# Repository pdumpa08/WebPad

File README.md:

# WebPad

WebPad is a macropad made for web developers everywhere. It uses a system of 5 custom-mapped keys to offer developers the increased efficiency you need when on a tight deadline. It also includes two RGB LEDs (for that extra coolness factor) and uses KMK firmware to control everything.

## Features:
- 3D printed case
- 2RGB SK6812MINI LEDs for underglow (open to customization)
- 5 custom-mapped keys (Cherry MX keys)
- All code using kmk firmware (easy to modfiy if you know Python)

## CAD Model:
Everything fits together using 4 M3 screws and heatset inserts, used on the case

It has 2 separate printed pieces: the top section and the bottom section. These sections fit together using the screws mentioned above. These designs were created on Fusion 360, with fit tests done for each of the parts (including with the PCB).

## PCB:
Below are my PCB design and schematic. I designed the schematic/PCB to match the needs of web developers, with 5 switches offering access to essential functions (described in the firmware section). Basic connection techniques like using both layers for traces were required and implemented. After a little research, I found that using a ground plane will likely improve functionality in this product.

## Firmware:
This hackpad uses KMK firmware for everything, from mapping the switches to controlling the LEDs. Specifically, the firmware currently offers this functionality:

- RGB LED backlighting
- refresh web page
- clear cache in a browser
- open elements in browser developer tools
- open responsive design mode
- start VSCode Live Server
- open console in developer tools

## BOM:

Here is everything you need to make this hackpad (All parts part of the approved kit)

- 5x Cherry MX Switches
- 5x DSA Keycaps
- 4x M3x5x4 Heatset inserts
- 4x M3x16mm screws
- 2x SK6812 MINI-E LEDs
- 1x XIAO RP2040
- 1x Case (2 printed parts)

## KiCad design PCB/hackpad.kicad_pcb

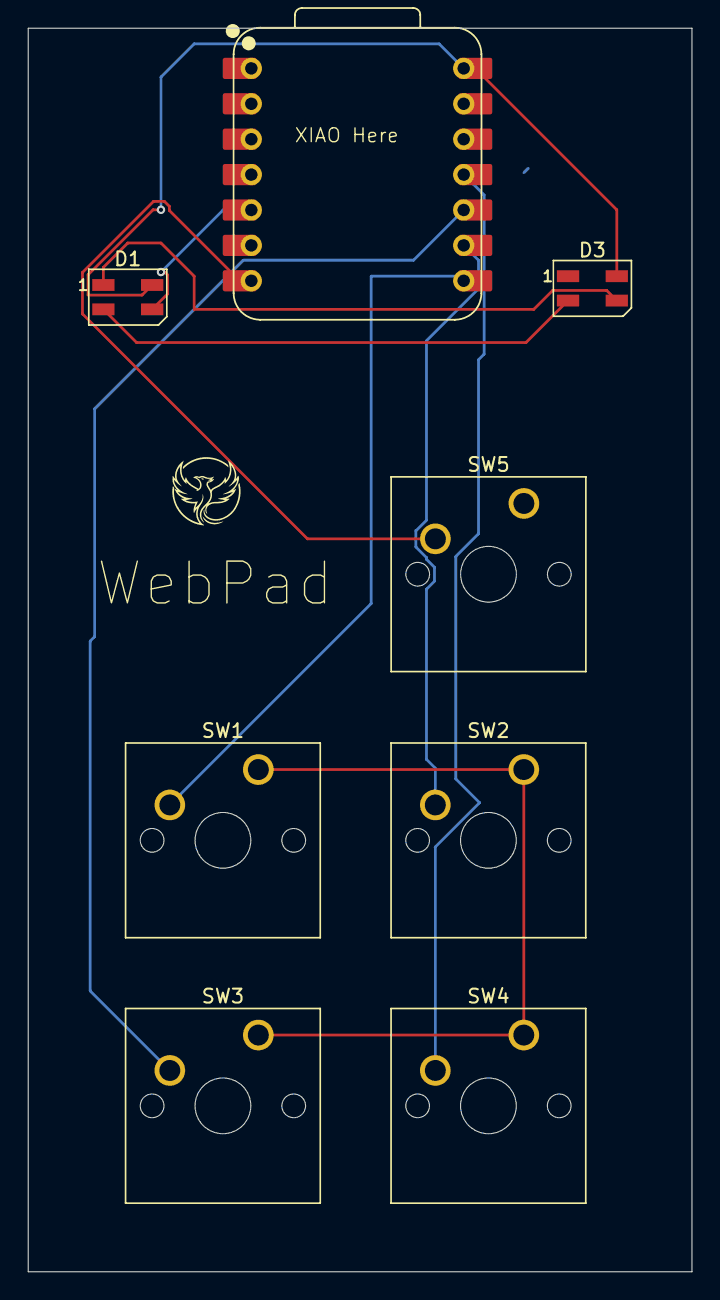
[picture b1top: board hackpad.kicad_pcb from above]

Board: 2 copper layers, 47.6 x 89.2 mm, 8 parts (0 on the bottom side), 10 nets.

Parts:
D1, D3: SK6812MINI; LED_SK6812MINI_PLCC4_3.5x3.5mm_P1.75mm
SW1, SW2, SW3, SW4, SW5: SW_Push; SW_Cherry_MX_1.00u_PCB
U1: XIAO-RP2040-DIP

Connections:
+5V: D1.4 (VDD), D3.4 (VDD), U1.14 (VBUS)
GND: SW1.1, SW2.1, SW3.1, SW4.1, SW5.1, U1.13 (GND)
unnamed: D1.3 (DIN), U1.5 (GPIO6/SDA)
unnamed: D1.1 (DOUT), D3.3 (DIN)
unnamed: D1.2 (VSS), D3.2 (VSS)
unnamed: SW5.2, U1.7 (GPIO0/TX)
unnamed: SW1.2, U1.8 (GPIO1/RX)
unnamed: SW2.2, U1.9 (GPIO2/SCK)
unnamed: SW4.2, U1.11 (GPIO3/MOSI)
unnamed: SW3.2, U1.10 (GPIO4/MISO)

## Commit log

2025-07-07 Add all files
2025-07-07 Add Readme Info
2025-07-07 Modify Readme Info
2025-07-07 Modify Readme Info and images
2025-07-08 Modify Readme
2025-07-08 Update file organization
2025-07-22 Modify CAD
